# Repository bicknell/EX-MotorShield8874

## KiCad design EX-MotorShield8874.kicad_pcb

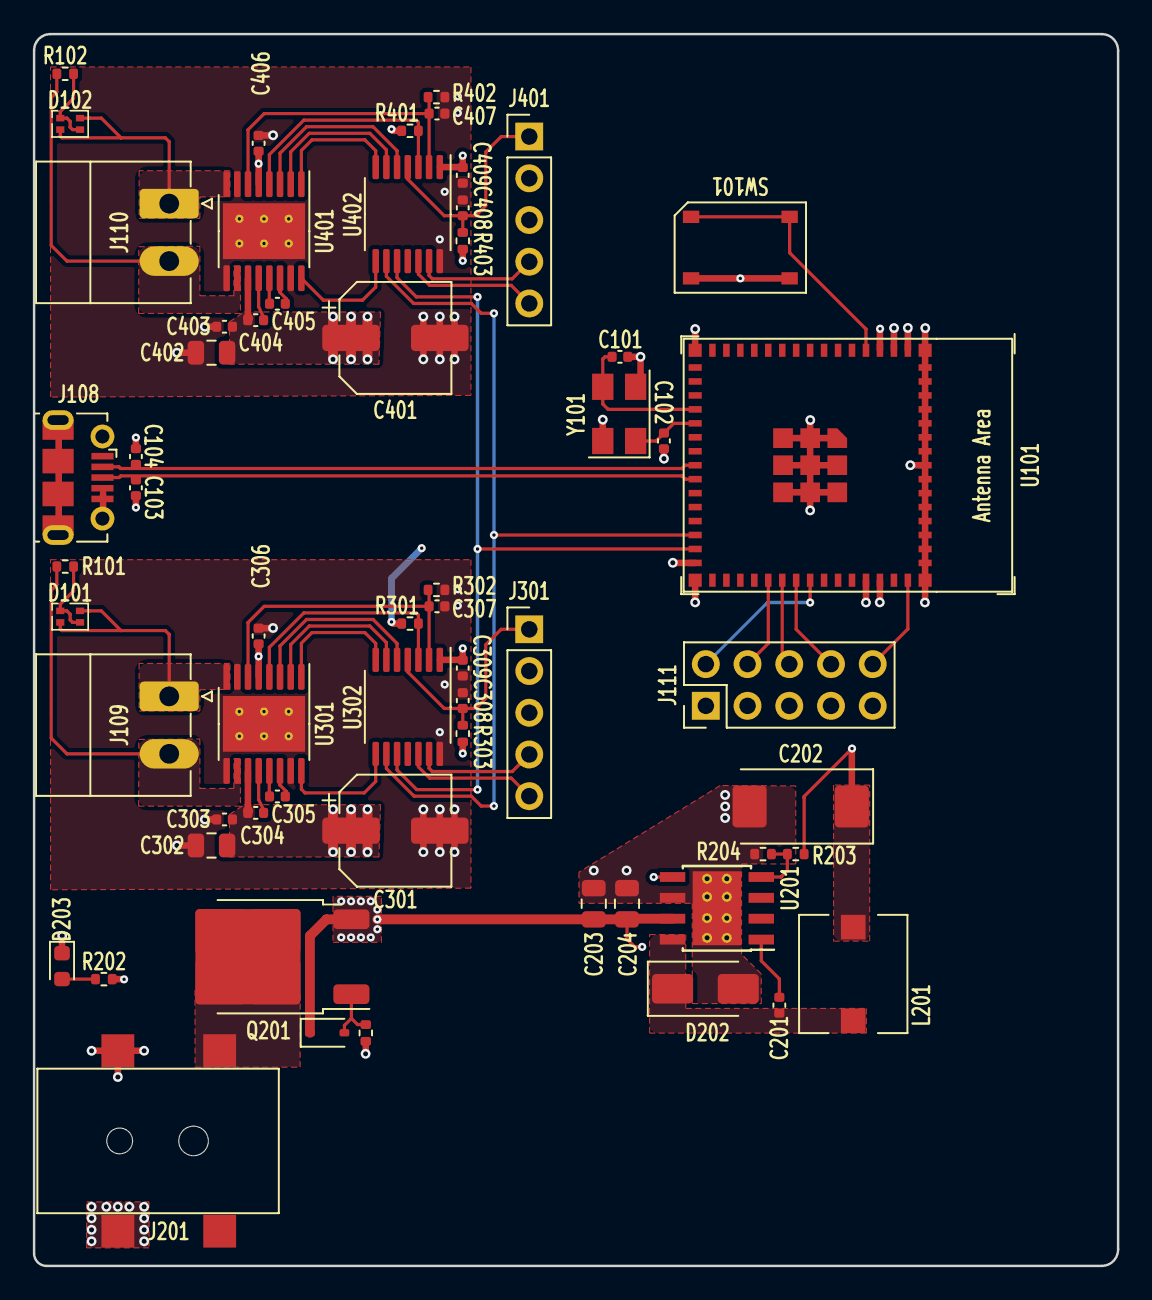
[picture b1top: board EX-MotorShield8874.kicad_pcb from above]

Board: 4 copper layers, 66.0 x 75.0 mm, 60 parts (0 on the bottom side), 51 nets.

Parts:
C101, C102, C103, C104: 20pF; C_0402_1005Metric
C201: 10nF; C_0402_1005Metric
C202: 220uF; CP_EIA-7343-31_Kemet-D
C203, C204: 4.7uF; C_0805_2012Metric
C301, C401: 100uF; CP_Elec_6.3x7.7
C302, C402: 10uF; C_0805_2012Metric
C303, C304, C306, C308, C309, C403, C404, C406, C408, C409: 100nF; C_0402_1005Metric
C305, C307, C405, C407: 22nF; C_0402_1005Metric
D101, D102: 18-225A; LED_LiteOn_LTST-C295K_1.6x0.8mm
D201: 10V; D_SOD-323
D202: B340A; D_SMA
D203: EMERALD; LED_0603_1608Metric
J108: USB_B_Micro; USB_Micro-B_Molex-105017-0001
J109, J110: MC 1,5/ 2-G-3,5; PhoenixContact_MC_1,5_2-G-3.5_1x02_P3.50mm_Horizontal
J111: JTAG; PinHeader_2x05_P2.54mm_Vertical
J201: Barrel_Jack_MountingPin; DC-S050-200
J301, J401: ICSP; PinHeader_1x05_P2.54mm_Vertical
L201: 22uH; L_6.7x7.2_H5
Q201: AOD4185; TO-252-2
R101, R102, R201, R202, R301, R401: 47K; R_0402_1005Metric
R203: 17K4; R_0402_1005Metric
R204, R303, R403: 10K; R_0402_1005Metric
R302, R402: 1K24; R_0402_1005Metric
SW101: FLASH; TS-1187A
U101: ESP32-S2-MINI-2U; ESP32-S2-MINI-1
U201: TPS5430DDA; TI_SO-PowerPAD-8_ThermalVias
U301, U401: DRV8874PWPR; HTSSOP-16-1EP_4.4x5mm_P0.65mm_EP3.4x5mm_Mask2.46x2.31mm_The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
U302, U402: PIC16F15224-I/ST; TSSOP-14_4.4x5mm_P0.65mm
Y101: 40Mhz; Crystal_SMD_5032-4Pin_5.0x3.2mm

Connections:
+3V3: C202.1, C306.1, C309.1, C406.1, C409.1, J111.1, J301.2, J401.2, L201.2, R202.2, R203.2, R301.1, R303.1, R401.1, R403.1, U101.3 (3V3), U301.5 (VRef), U302.1 (VDD), U401.5 (VRef), U402.1 (VDD)
/BOOT_MODE: SW101.1, U101.4 (GPIO0/BOOT)
/Output 1/CPH: C305.2, U301.13 (CPH)
/Output 1/CPL: C305.1, U301.14 (CPL)
/Output 1/EN/IN1: U301.1 (EN/IN1), U302.7 (~SS/PWM2/CLCIN0/C2IN3-/C1IN3-/AN7/RC3)
/Output 1/PH/IN2: U301.2 (PH/IN2), U302.6 (CLC2IN1/CWG1B/C2OUT/RC4)
/Output 1/PMODE: U301.16 (PMODE), U302.8 (SDO/C2IN2-/C1IN2-/AN6/RC2)
/Output 1/VCP: C304.2, U301.12 (VCP)
/Output 1/VPROPI: C307.1, R302.1, U301.6 (IPROPI), U302.2 (RA5/T1CKI/NCO1CLK/CLCIN1/CLKIN)
/Output 1/nFault: R301.2, U301.4 (nFAULT), U302.3 (RA4/AN3/T1G/NCO1/SDO/CLKOUT)
/Output 1/nSleep: U301.3 (nSleep), U302.5 (PWM1/CLC1/CWG1A/RC5)
/Output 2/CPH: C405.2, U401.13 (CPH)
/Output 2/CPL: C405.1, U401.14 (CPL)
/Output 2/EN/IN1: U401.1 (EN/IN1), U402.7 (~SS/PWM2/CLCIN0/C2IN3-/C1IN3-/AN7/RC3)
/Output 2/PH/IN2: U401.2 (PH/IN2), U402.6 (CLC2IN1/CWG1B/C2OUT/RC4)
/Output 2/PMODE: U401.16 (PMODE), U402.8 (SDO/C2IN2-/C1IN2-/AN6/RC2)
/Output 2/VCP: C404.2, U401.12 (VCP)
/Output 2/VPROPI: C407.1, R402.1, U401.6 (IPROPI), U402.2 (RA5/T1CKI/NCO1CLK/CLCIN1/CLKIN)
/Output 2/nFault: R401.2, U401.4 (nFAULT), U402.3 (RA4/AN3/T1G/NCO1/SDO/CLKOUT)
/Output 2/nSleep: U401.3 (nSleep), U402.5 (PWM1/CLC1/CWG1A/RC5)
/Power/boot: C201.1, U201.1 (BOOT)
/Power/gate: D201.2 (A), Q201.1 (G), R201.1
/Power/ph: C201.2, D202.1 (K), L201.1, U201.8 (PH)
/Power/v_conn: J201.1, Q201.2 (D)
/Power/vsense: R203.1, R204.2, U201.4 (VSENSE)
/SCL: U101.29 (GPIO34), U302.10 (SCK/SCL/CLC2/C2IN+/AN4/RC0), U402.10 (SCK/SCL/CLC2/C2IN+/AN4/RC0)
/SDA: U101.28 (GPIO33), U302.9 (SDI/SDA/PWM4/NCO1/C2IN1-/C1IN1-/AN5/RC1), U402.9 (SDI/SDA/PWM4/NCO1/C2IN1-/C1IN1-/AN5/RC1)
/TCK: J111.4, U101.35 (MTCK/JTAG/GPIO39)
/TDI: J111.8, U101.37 (MTDI/JTAG/GPIO41)
/TDO: J111.6, U101.36 (MTDO/JTAG/GPIO40)
/TMS: J111.2, U101.38 (MTMS/JTAG/GPIO42)
/USB_D+: C103.1, J108.3 (D+), U101.24 (USB_D+/ADC2_CH9/GPIO20)
/USB_D-: C104.1, J108.2 (D-), U101.23 (USB_D-/ADC2_CH8/GPIO19)
/trk1l: D101.2 (A2), D101.3 (K1), J109.1, U301.8 (OUT1)
/trk1r: J109.2, R101.2, U301.10 (OUT2)
/trk2l: D102.2 (A2), D102.3 (K1), J110.1, U401.8 (OUT1)
/trk2r: J110.2, R102.2, U401.10 (OUT2)
/~SRST: J111.10, U101.45 (CHIP/PU/RESET)
GND: C101.2, C102.2, C103.2, C104.2, C202.2, C203.2, C204.2, C301.2, C302.2, C303.2, C306.2, C307.2, C308.2, C309.2, C401.2, C402.2, C403.2, C406.2, C407.2, C408.2, C409.2, D202.2 (A), D203.1 (K), J108.4 (ID), J108.5 (GND), J108.6 (Shield), J111.3, J111.5, J111.9, J201.2, J201.MP (MountPin), J301.3, J401.3, R201.2, R204.1, R302.2, R402.2, SW101.2, U101.1 (GND), U101.2 (GND), U101.30 (GND), U101.42 (GND), U101.43 (GND), U101.46 (GND), U101.47 (GND), U101.48 (GND), U101.49 (GND), U101.50 (GND), U101.51 (GND), U101.52 (GND), U101.53 (GND), U101.54 (GND), U101.55 (GND), U101.56 (GND), U101.57 (GND), U101.58 (GND), U101.59 (GND), U101.60 (GND), U101.61 (GND), U101.62 (GND), U101.63 (GND), U101.64 (GND), U101.65 (GND), U201.6 (GND), U201.9 (GNDPAD), U301.7 (IMODE), U301.9 (GND), U301.15 (GND), U301.17 (GND), U302.14 (VSS), U401.7 (IMODE), U401.9 (GND), U401.15 (GND), U401.17 (GND), U402.14 (VSS), Y101.2, Y101.4
unnamed: D101.1 (A1), D101.4 (K2), R101.1
unnamed: D102.1 (A1), D102.4 (K2), R102.1
unnamed: D203.2 (A), R202.1
unnamed: C308.1, J301.1, R303.2, U302.4 (RA3/T1G/CLC1IN0/~SS/~MCLR/Vpp)
unnamed: J301.4, U302.13 (RA0/AN0/DACOUT1/C1IN+/ICSPDAT)
unnamed: J301.5, U302.12 (RA1/AN1/Vref+/C1IN0-/C2IN0-/ICSPCLK)
unnamed: C408.1, J401.1, R403.2, U402.4 (RA3/T1G/CLC1IN0/~SS/~MCLR/Vpp)
unnamed: J401.4, U402.13 (RA0/AN0/DACOUT1/C1IN+/ICSPDAT)
unnamed: J401.5, U402.12 (RA1/AN1/Vref+/C1IN0-/C2IN0-/ICSPCLK)
unnamed: C101.1, U101.19 (GPIO15/ADC2_CH4/XTAL_32K_P), Y101.3
unnamed: C102.1, U101.20 (GPIO16/ADC2_CH5/XTAL_32K_N), Y101.1
Vdrive: C203.1, C204.1, C301.1, C302.1, C303.1, C304.1, C401.1, C402.1, C403.1, C404.1, D201.1 (K), Q201.3 (S), U201.5 (EN), U201.7 (VIN), U301.11 (VM), U401.11 (VM)

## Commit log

2023-11-14 Convert to native KiCad & rework BOM to JLCPCB Basic Parts.
    1) Use a KiCad template for an Arduino motor shield as the base.
    2) DC-DC Buck converter shows no longer available, select new
    component from JLCPCB's basic list and re-work circuit as necessary.
    3) Reworked BOM to use as many JLCPCB basic components as possible.
    4) Reworked BOM so all components are in-stock at JLCPCB.
    5) Switched to TSSOP for the 74HC logic to save space.e
2023-11-14 Added two pin header parts to the BOM.
2023-11-15 Trace/via size consistency, better defaults, minor trace cleanup.
    1) Set up Net Classes with default trace and via sizes.
    2) Set all traces/vias to consistent sizes based on NetClass.
    3) Minor trace re-routing based on the changes above.
    4) Added a documentation block on pours and priorities.
    Checked DRC again.
2023-11-15 First attempt at making the A or B pinout "one jumper" configurable.
2023-11-15 Replaced the OpAmp comparitor circuit with a single MOSFET.
2023-11-16 IOREF detection to MOSFET, new indicator LEDs, reduce capacitor size.
    1) Replaced the OpAmp & passives that determined IOREF 3 or 5 with a
    P-Channel MOSFET that does the same thing for less cost, components,
    and board space.
    2) Changed indicator LEDs to be RED/GREEN single units. When on DCC
    they will light RED+GREEN = YELLOW. When driving a DC load (e.g.
    a motor, or even DC track with PWM) they will light either RED or
2023-11-16 Add part numbers for stacking headers.
    The stacking headers can be found via global sourcing and hand soldered
    by JLCPCB. Add the part numbers to the BOM.
2023-11-17 Turn off data sheet links.
    For some reason data sheet links on the schematic were enabled on the
    standard Arduino headers in the template. I didn't notice when I filled
    them in on the BOM they showed up on the schematic. This turns them back
    off.
2023-11-17 Reworked schematic to include an ESP32-S2-MINI-2.
    Reworked schematic to include an ESP32-S2-MINI-2 as the main CPU.
    Two track outputs are directly on this board. The rest of the GPIO
    pins are routed so that the existing EX-MotorShield8874 can stack.
    The result is potentially 6 power outputs from a single unit.
    Added a USB interface to the module.
    Moved the drivers into heirarchal sheets.
2023-11-17 Update BOM to include all parts.
2023-11-17 Initial attempt to route the board.
2023-11-19 Stand alone, purpose build command station doodle.
